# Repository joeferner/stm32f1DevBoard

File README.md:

# STM32F1xxx Dev Board

STM32F1xxx ARM Dev board with Microchip MRF24WB0MA WiFi and SD Card.

## Resources

* [Programming STM32 F2, F4 ARMs under Linux: A Tutorial from Scratch](http://www.triplespark.net/elec/pdev/arm/stm32.html)
* [stm32flash](http://code.google.com/p/stm32flash/)

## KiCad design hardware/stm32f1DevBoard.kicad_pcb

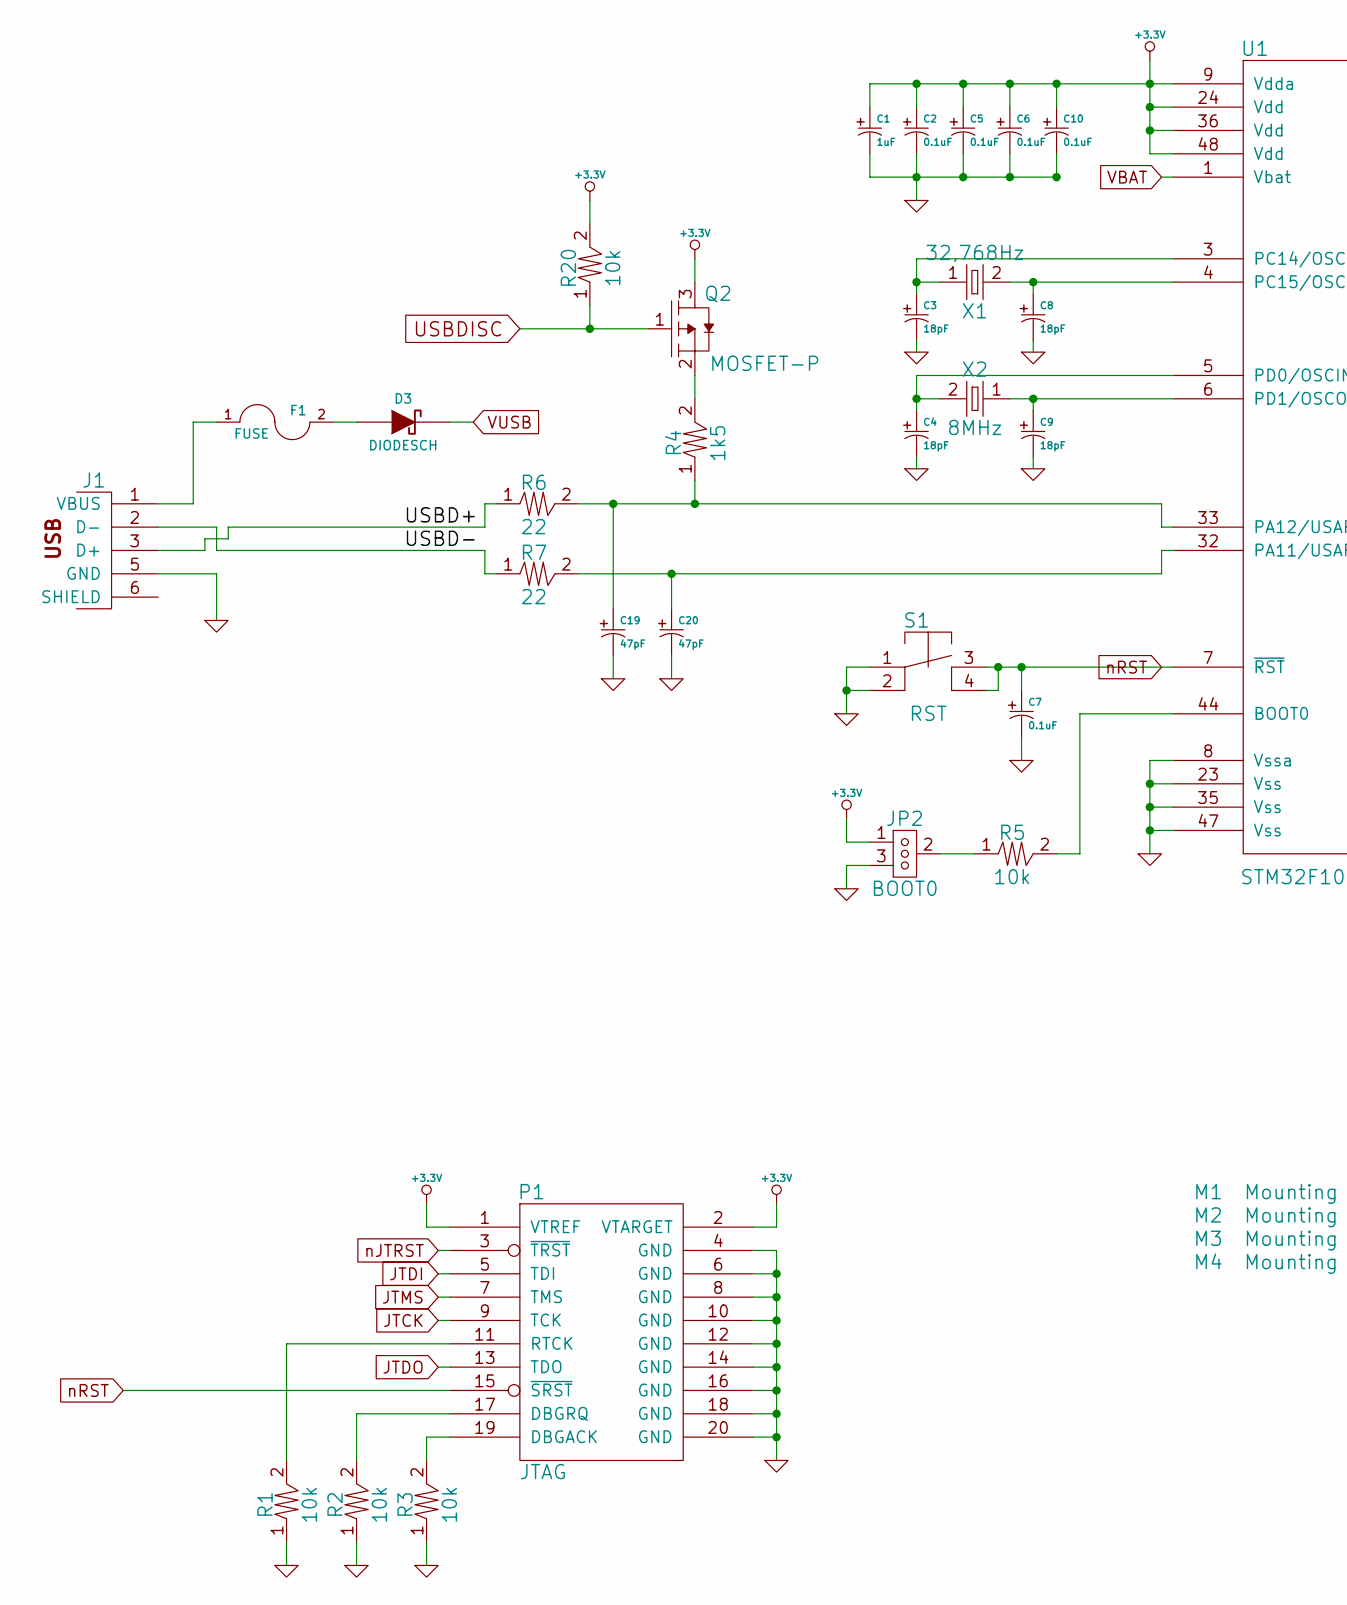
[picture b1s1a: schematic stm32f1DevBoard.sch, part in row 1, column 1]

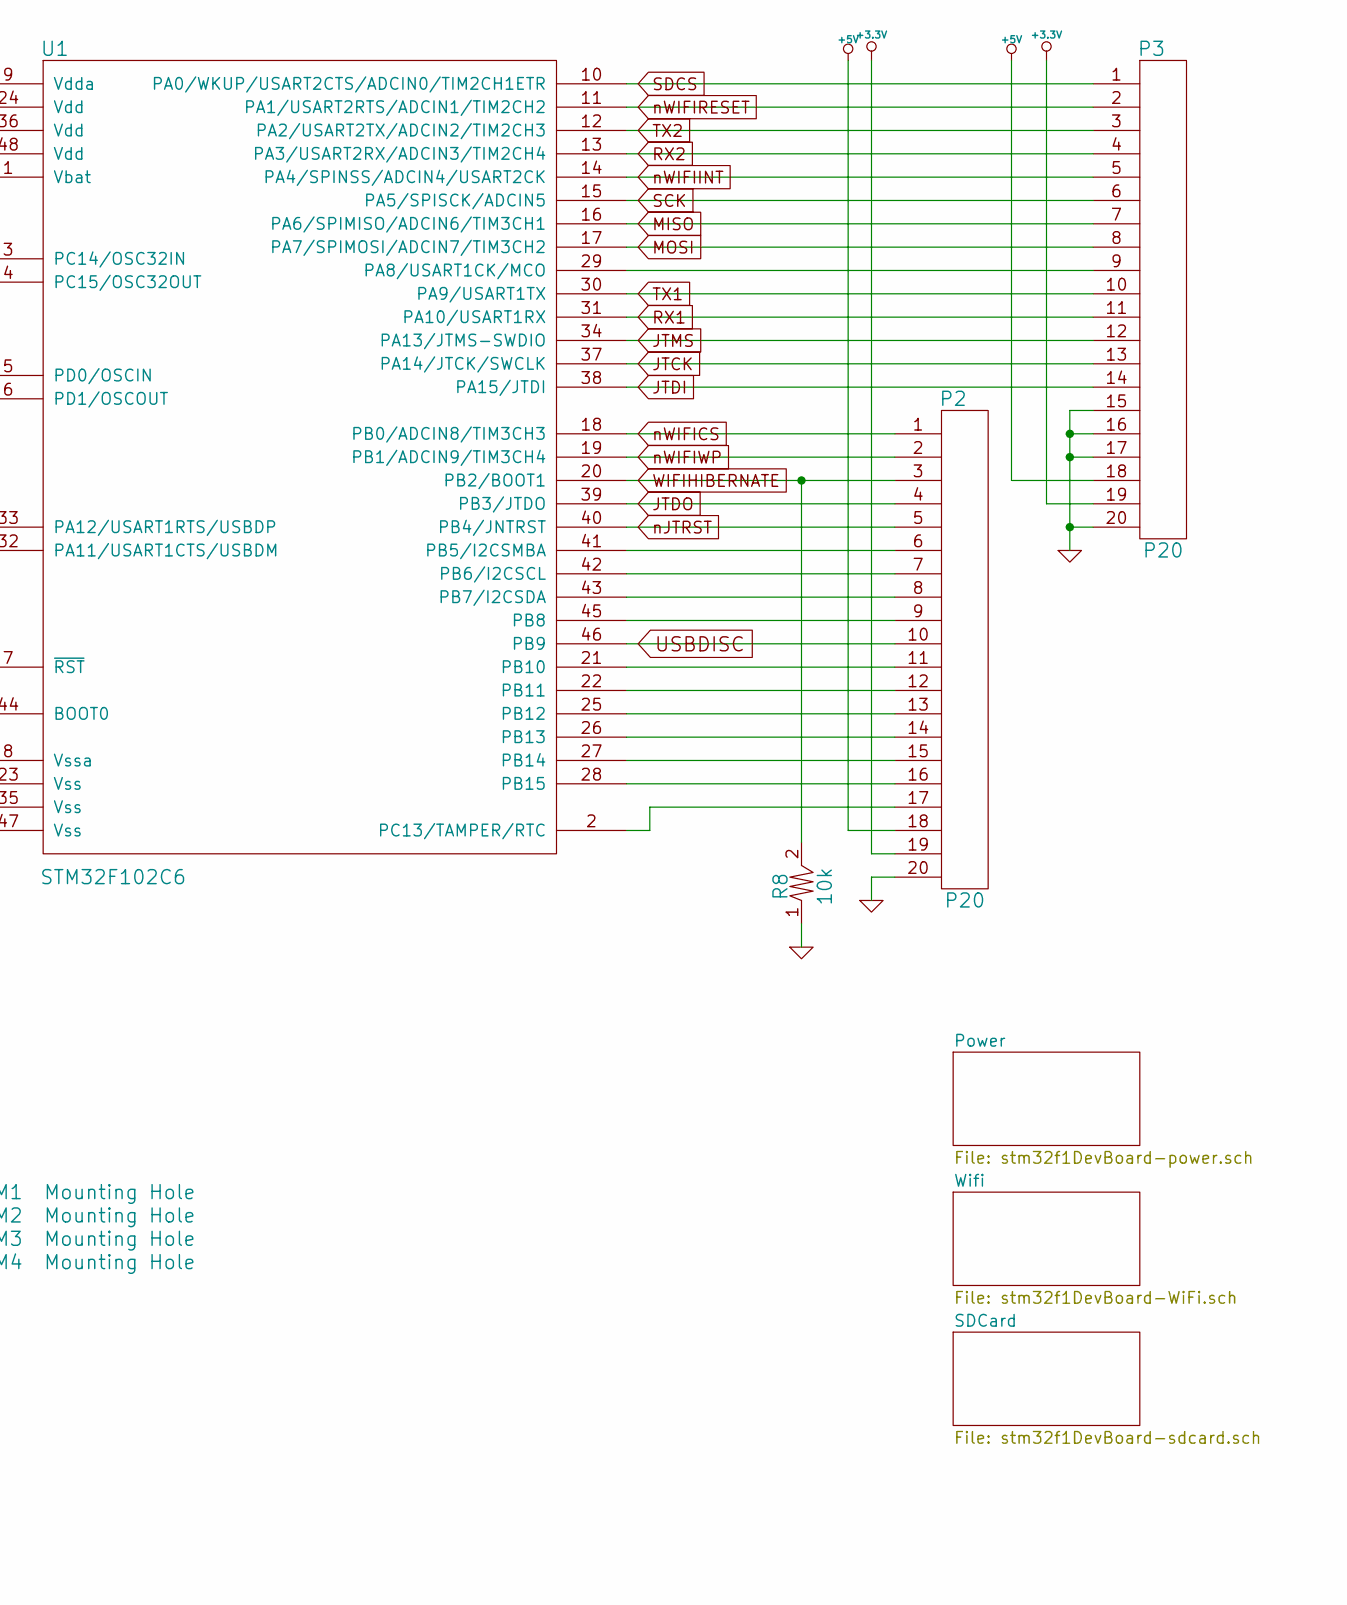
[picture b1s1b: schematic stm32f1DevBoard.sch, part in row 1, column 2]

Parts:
C1: 1uF
C2, C5, C6, C7, C10: 0.1uF
C3, C4, C8, C9: 18pF
C19, C20: 47pF
D3: DIODESCH
F1: FUSE
J1: USB_2
JP2: BOOT0
M1, M2, M3, M4: Mounting Hole
P1: JTAG
P2, P3: P20
Q2: MOSFET-P
R1, R2, R3, R5, R8, R20: 10k
R4: 1k5
R6, R7: 22
S1: RST
U1: STM32F102C6
X1: 32,768Hz
X2: 8MHz

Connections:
+3.3V: C1.1, C2.1, C5.1, C6.1, C10.1, JP2.1, P1.1 (VTREF), P1.2 (VTARGET), P2.19, P3.19, Q2.3, R20.2, U1.9 (Vdda), U1.24 (Vdd), U1.36 (Vdd), U1.48 (Vdd); also elsewhere on the board
+5V: P2.18, P3.18; also elsewhere on the board
/USBD+: J1.3 (D+), R6.1
/USBD-: J1.2 (D-), R7.1
GND: C1.2, C2.2, C3.2, C4.2, C5.2, C6.2, C7.2, C8.2, C9.2, C10.2, C19.2, C20.2, J1.5 (GND), JP2.3, P1.4 (GND), P1.6 (GND), P1.8 (GND), P1.10 (GND), P1.12 (GND), P1.14 (GND), P1.16 (GND), P1.18 (GND), P1.20 (GND), P2.20, P3.15, P3.16, P3.17, P3.20, R1.1, R2.1, R3.1, R8.1, S1.1, S1.2, U1.8 (Vssa), U1.23 (Vss), U1.35 (Vss), U1.47 (Vss); also elsewhere on the board
JTCK: P1.9 (TCK), P3.13, U1.37 (PA14/JTCK/SWCLK)
JTDI: P1.5 (TDI), P3.14, U1.38 (PA15/JTDI)
JTDO: P1.13 (TDO), P2.4, U1.39 (PB3/JTDO)
JTMS: P1.7 (TMS), P3.12, U1.34 (PA13/JTMS-SWDIO)
MISO: P3.7, U1.16 (PA6/SPIMISO/ADCIN6/TIM3CH1); also elsewhere on the board
MOSI: P3.8, U1.17 (PA7/SPIMOSI/ADCIN7/TIM3CH2); also elsewhere on the board
unnamed: P3.9, U1.29 (PA8/USART1CK/MCO)
unnamed: P2.16, U1.28 (PB15)
unnamed: P2.15, U1.27 (PB14)
unnamed: P2.14, U1.26 (PB13)
unnamed: P2.9, U1.45 (PB8)
unnamed: P2.13, U1.25 (PB12)
unnamed: P2.8, U1.43 (PB7/I2CSDA)
unnamed: P2.17, U1.2 (PC13/TAMPER/RTC)
unnamed: P2.12, U1.22 (PB11)
unnamed: P2.11, U1.21 (PB10)
unnamed: P2.7, U1.42 (PB6/I2CSCL)
unnamed: P2.6, U1.41 (PB5/I2CSMBA)
unnamed: C3.1, U1.3 (PC14/OSC32IN), X1.1
unnamed: D3.1 (A), F1.2
unnamed: F1.1, J1.1 (VBUS)
unnamed: Q2.2, R4.2
unnamed: P1.11 (RTCK), R1.2
unnamed: P1.19 (DBGACK), R3.2
unnamed: P1.17 (DBGRQ), R2.2
unnamed: C20.1, R7.2, U1.32 (PA11/USART1CTS/USBDM)
unnamed: C8.1, U1.4 (PC15/OSC32OUT), X1.2
unnamed: C4.1, U1.5 (PD0/OSCIN), X2.2
unnamed: R5.2, U1.44 (BOOT0)
unnamed: JP2.2, R5.1
unnamed: C19.1, R4.1, R6.2, U1.33 (PA12/USART1RTS/USBDP)
unnamed: C9.1, U1.6 (PD1/OSCOUT), X2.1
RX1: P3.11, U1.31 (PA10/USART1RX)
RX2: P3.4, U1.13 (PA3/USART2RX/ADCIN3/TIM2CH4)
SCK: P3.6, U1.15 (PA5/SPISCK/ADCIN5); also elsewhere on the board
SDCS: P3.1, U1.10 (PA0/WKUP/USART2CTS/ADCIN0/TIM2CH1ETR); also elsewhere on the board
TX1: P3.10, U1.30 (PA9/USART1TX)
TX2: P3.3, U1.12 (PA2/USART2TX/ADCIN2/TIM2CH3)
USBDISC: P2.10, Q2.1, R20.1, U1.46 (PB9)
VBAT: U1.1 (Vbat); also elsewhere on the board
VUSB: D3.2 (K); also elsewhere on the board
WIFIHIBERNATE: P2.3, R8.2, U1.20 (PB2/BOOT1); also elsewhere on the board
nJTRST: P1.3 (~TRST), P2.5, U1.40 (PB4/JNTRST)
nRST: C7.1, P1.15 (~SRST), S1.3, S1.4, U1.7 (~RST)
nWIFICS: P2.1, U1.18 (PB0/ADCIN8/TIM3CH3); also elsewhere on the board
nWIFIINT: P3.5, U1.14 (PA4/SPINSS/ADCIN4/USART2CK); also elsewhere on the board
nWIFIRESET: P3.2, U1.11 (PA1/USART2RTS/ADCIN1/TIM2CH2); also elsewhere on the board
nWIFIWP: P2.2, U1.19 (PB1/ADCIN9/TIM3CH4); also elsewhere on the board

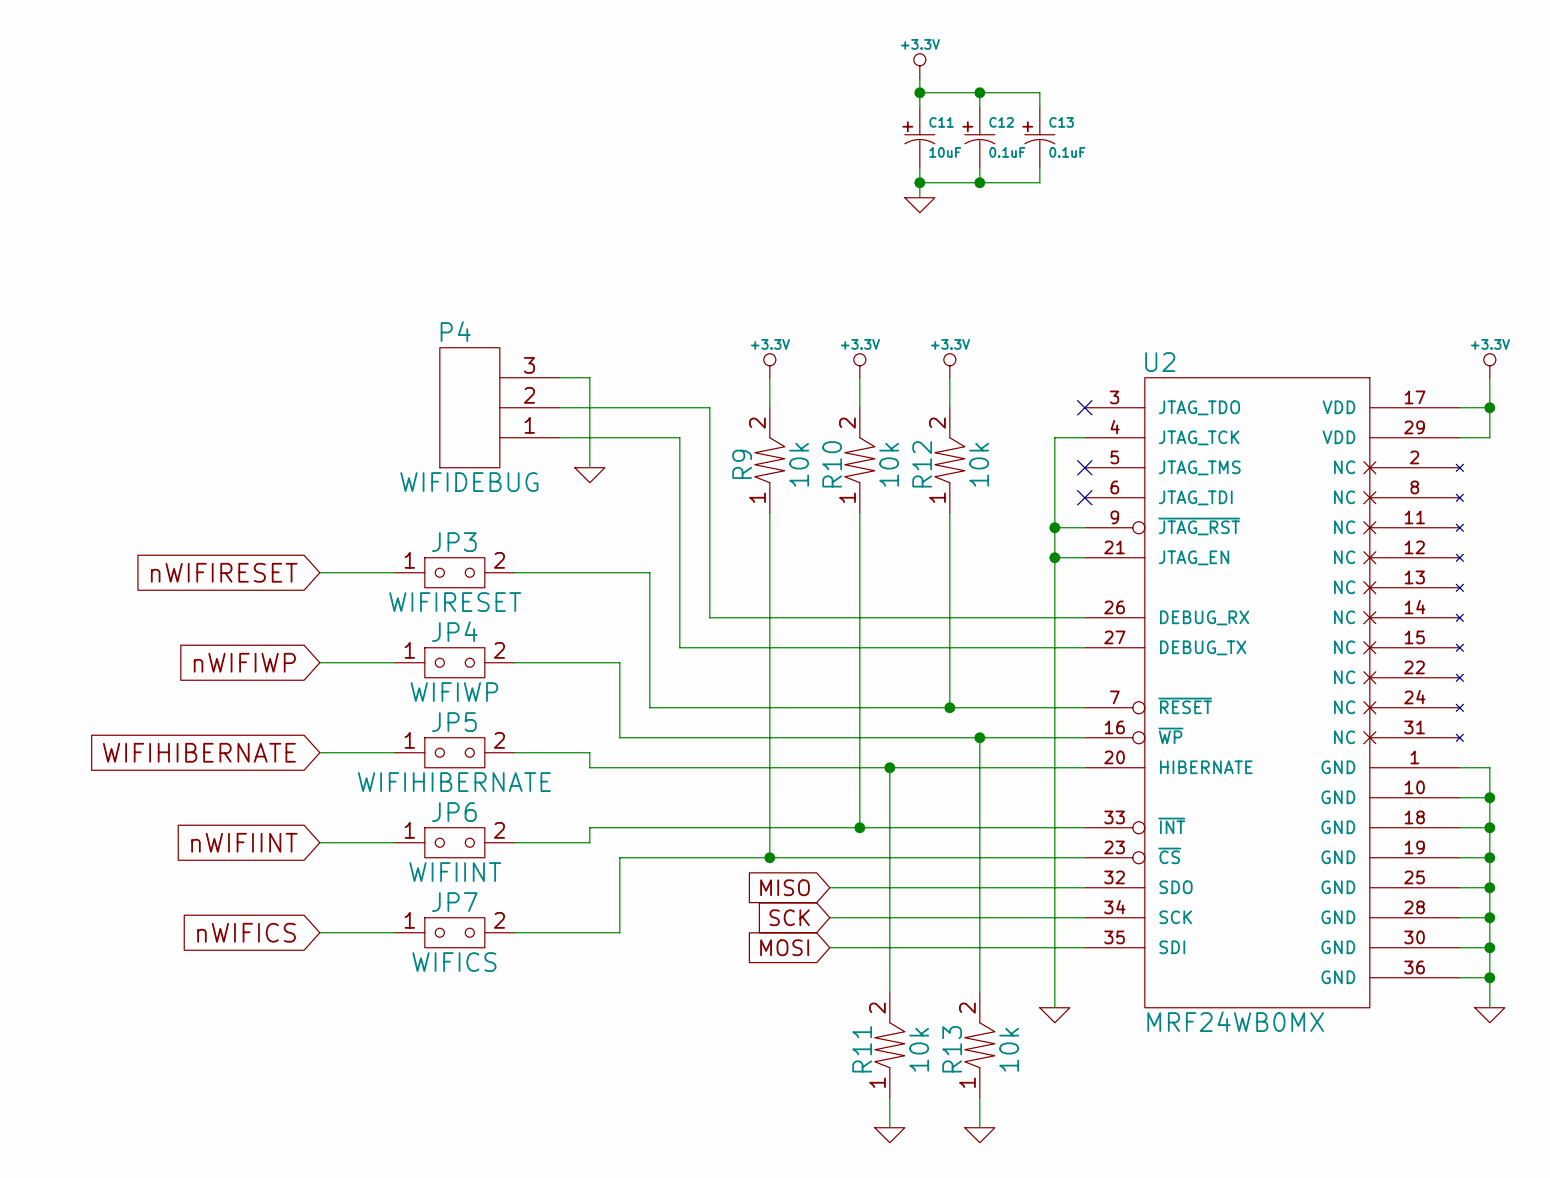
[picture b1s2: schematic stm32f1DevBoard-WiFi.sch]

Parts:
C11: 10uF
C12, C13: 0.1uF
JP3: WIFIRESET
JP4: WIFIWP
JP5: WIFIHIBERNATE
JP6: WIFIINT
JP7: WIFICS
P4: WIFIDEBUG
R9, R10, R11, R12, R13: 10k
U2: MRF24WB0MX

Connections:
+3.3V: C11.1, C12.1, C13.1, R9.2, R10.2, R12.2, U2.17 (VDD), U2.29 (VDD); also elsewhere on the board
GND: C11.2, C12.2, C13.2, P4.3, R11.1, R13.1, U2.1 (GND), U2.4 (JTAG_TCK), U2.9 (~JTAG_RST), U2.10 (GND), U2.18 (GND), U2.19 (GND), U2.21 (JTAG_EN), U2.25 (GND), U2.28 (GND), U2.30 (GND), U2.36 (GND); also elsewhere on the board
MISO: U2.32 (SDO); also elsewhere on the board
MOSI: U2.35 (SDI); also elsewhere on the board
unnamed: JP4.2, R13.2, U2.16 (~WP)
unnamed: JP5.2, R11.2, U2.20 (HIBERNATE)
unnamed: JP3.2, R12.1, U2.7 (~RESET)
unnamed: JP7.2, R9.1, U2.23 (~CS)
unnamed: JP6.2, R10.1, U2.33 (~INT)
unnamed: P4.2, U2.26 (DEBUG_RX)
unnamed: P4.1, U2.27 (DEBUG_TX)
SCK: U2.34 (SCK); also elsewhere on the board
WIFIHIBERNATE: JP5.1; also elsewhere on the board
nWIFICS: JP7.1; also elsewhere on the board
nWIFIINT: JP6.1; also elsewhere on the board
nWIFIRESET: JP3.1; also elsewhere on the board
nWIFIWP: JP4.1; also elsewhere on the board

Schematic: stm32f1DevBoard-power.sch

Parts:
BT1: BATTERY
C14, C18: 100uF
C15, C16: 10uF
D1: DIODESCH
D2: POWERLED
J2: POWER_JACK
JP8: BATTERYENABLE
Q1: MOSFET-P
R14: 68k
R15: 33k
R16, R17: 10k
R18: 100
U3: LM358
U4: VREG-X-5
U5: VREG-5-3.3

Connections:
+3.3V: C16.1, C18.1, JP8.1, R18.1, U5.2 (VO), U5.4 (TAB); also elsewhere on the board
+5V: C14.1, C15.1, Q1.2, R16.2, U3.8 (V+), U4.3 (VO), U5.3 (VI); also elsewhere on the board
GND: BT1.2 (-), C14.2, C15.2, C16.2, C18.2, D2.2 (K), J2.2, J2.3, R15.1, R17.1, U3.4 (V-), U4.2 (GND), U4.4 (TAB), U5.1 (GND); also elsewhere on the board
unnamed: D2.1 (A), R18.2
unnamed: R14.1, R15.2, U3.3 (+)
unnamed: R16.1, R17.2, U3.2 (-)
unnamed: U3.1, U3.5 (+)
unnamed: Q1.1, U3.6 (-), U3.7
unnamed: BT1.1 (+), JP8.3
unnamed: D1.1 (A), J2.1
VBAT: JP8.2; also elsewhere on the board
VIN: D1.2 (K), R14.2, U4.1 (VI)
VUSB: Q1.3; also elsewhere on the board

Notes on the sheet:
Pin2 = 2.5V Pin3 = 2.5V at 7.65V

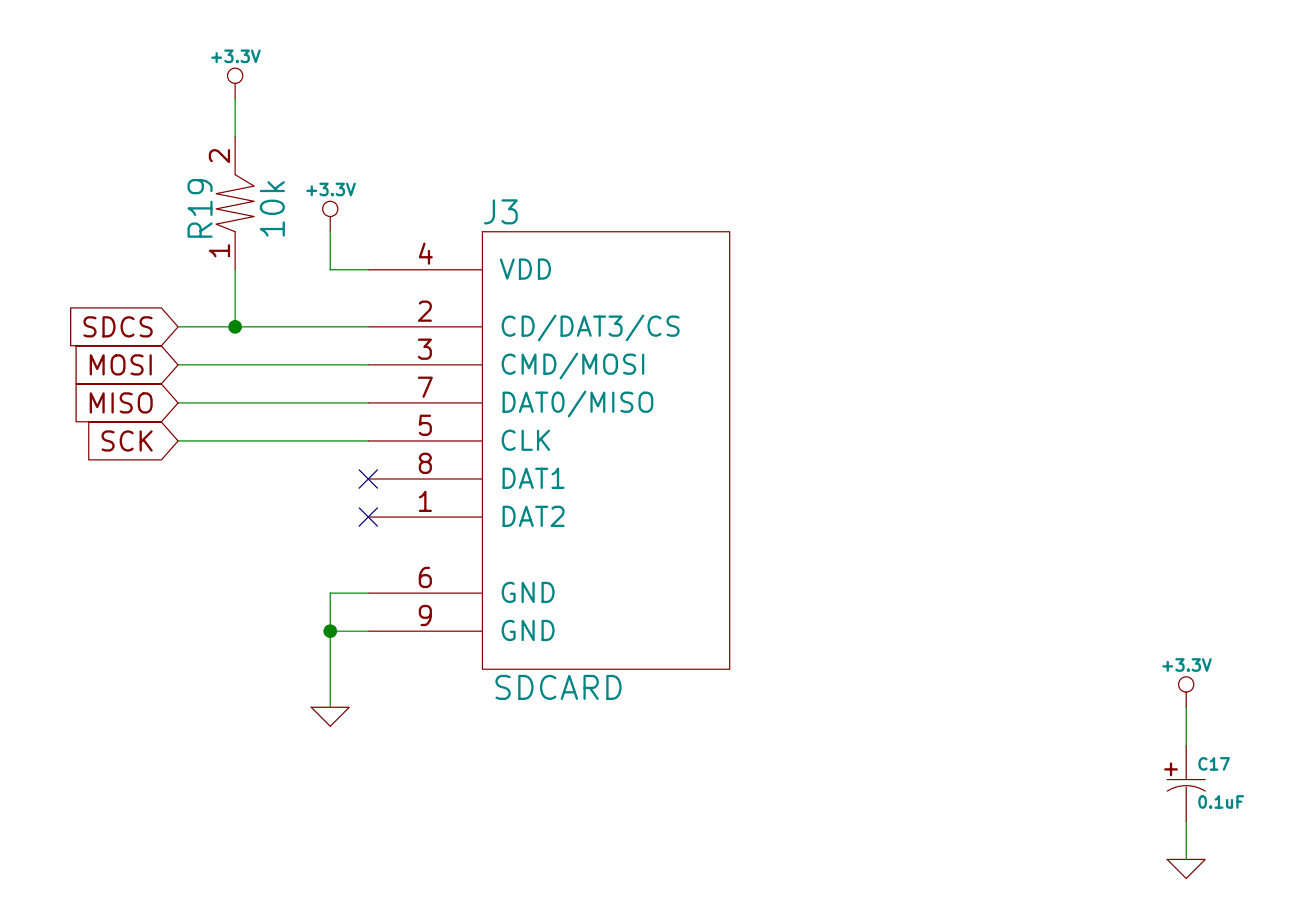
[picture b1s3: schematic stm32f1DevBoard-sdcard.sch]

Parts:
C17: 0.1uF
J3: SDCARD
R19: 10k

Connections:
+3.3V: C17.1, J3.4 (VDD), R19.2; also elsewhere on the board
GND: C17.2, J3.6 (GND), J3.9 (GND); also elsewhere on the board
MISO: J3.7 (DAT0/MISO); also elsewhere on the board
MOSI: J3.3 (CMD/MOSI); also elsewhere on the board
SCK: J3.5 (CLK); also elsewhere on the board
SDCS: J3.2 (CD/DAT3/CS), R19.1; also elsewhere on the board

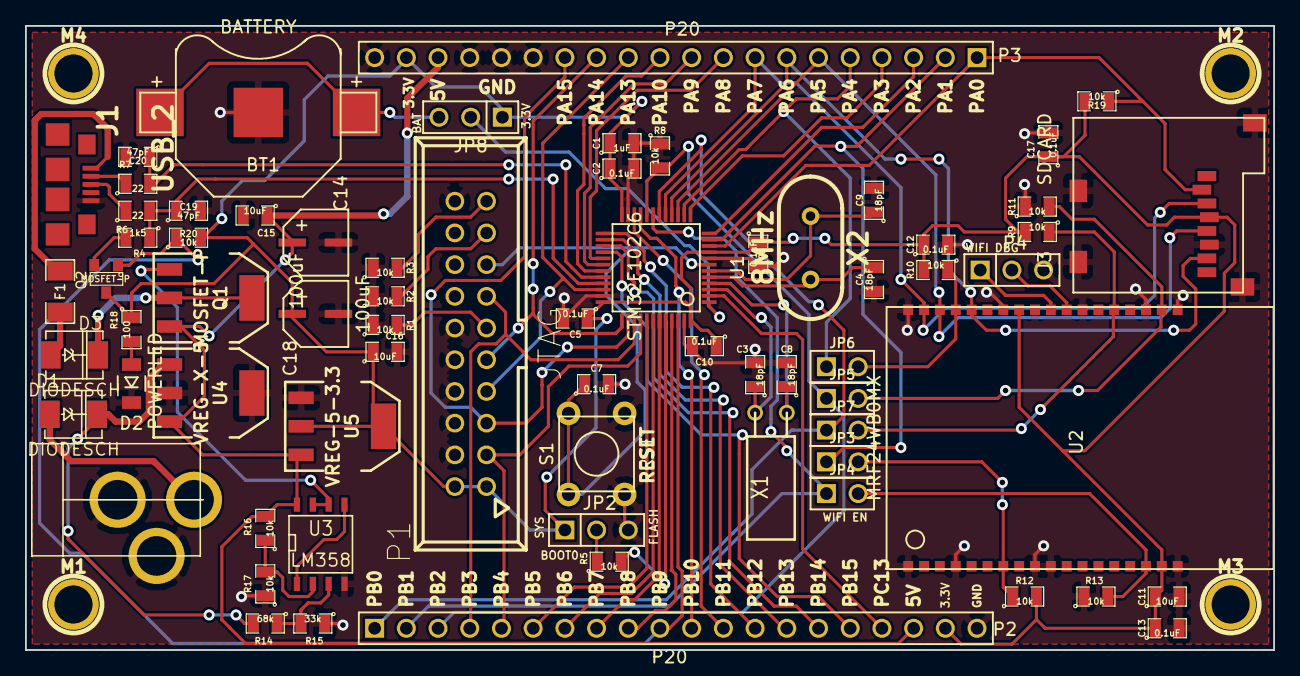
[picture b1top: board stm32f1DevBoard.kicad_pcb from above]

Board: 2 copper layers, 100.0 x 50.0 mm, 73 parts (0 on the bottom side), 68 nets.

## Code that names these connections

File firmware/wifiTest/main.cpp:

#include <wirish/wirish.h>
#include <mrf24w/mrf24w.h>
#include <string.h>

#define SDCARD_CS           PA0
#define SDCARD_SPI          1

#define WIFI_CS             PB0
#define WIFI_INT            PA4
#define WIFI_CONNECTION_LED PB5
#define WIFI_RESET          PA1
#define WIFI_WP             PB1
#define WIFI_HIBERNATE      PB2
#define WIFI_SPI            SDCARD_SPI

#define ECHO_PORT 8000

uint8_t wifiLocalIp[] = {192, 168, 1, 99};
uint8_t wifiGatewayIp[] = {192, 168, 1, 1};
uint8_t wifiSubnetMask[] = {255, 255, 255, 0};
const char* wifiSSID = "STMWIFI"; //"STMTEST";
const char* wifiSecurityPassphrase = "";
uint8_t wifiSecurityType = WF_SECURITY_OPEN;
uint8_t wifiWirelessMode = WF_INFRASTRUCTURE; //WF_ADHOC;

HardwareSPI spi1(WIFI_SPI);
Mrf24w wifi(spi1, WIFI_CS, WIFI_INT);

void wifiProcessEvent(uint8_t event, uint16_t eventInfo, uint8_t* extraInfo);

void setup() {
  Serial1.begin(19200);
  Serial1.println("begin");

  enableDebugPorts();
  //delay(5000);
  //disableDebugPorts();

  pinMode(SDCARD_CS, OUTPUT);
  digitalWrite(SDCARD_CS, HIGH);
  pinMode(WIFI_CS, OUTPUT);
  digitalWrite(WIFI_CS, HIGH);

  pinMode(WIFI_RESET, OUTPUT);
  pinMode(WIFI_HIBERNATE, OUTPUT);
  digitalWrite(WIFI_HIBERNATE, LOW);
  pinMode(WIFI_WP, OUTPUT);
  digitalWrite(WIFI_WP, LOW);
  pinMode(WIFI_CONNECTION_LED, OUTPUT);
  digitalWrite(WIFI_CONNECTION_LED, LOW);
  spi1.begin(SPI_4_5MHZ, MSBFIRST, 0);

  Serial1.println("wifi setup");
  digitalWrite(WIFI_RESET, LOW);
  delay(100);
  digitalWrite(WIFI_RESET, HIGH);

  wifi.setProcessEventFn(wifiProcessEvent);
  Serial1.println("wifi begin");
  wifi.setLocalIp(wifiLocalIp);
  wifi.setGatewayIp(wifiGatewayIp);
  wifi.setSubnetMask(wifiSubnetMask);
  wifi.setSSID(wifiSSID);
  wifi.setSecurityPassphrase(wifiSecurityPassphrase);
  wifi.setSecurityType(wifiSecurityType);
  wifi.setWirelessMode(wifiWirelessMode);
  wifi.begin();
  Serial1.println("wifi begin complete");

  //wifi.scan(WF_SCAN_ALL);

  wifi.connect();

  //uip_listen(HTONS(ECHO_PORT));
}

int ssss = 0;
struct uip_udp_conn *c;

void loop() {
  wifi.loop();

  while (Serial1.available() > 0) {
    uint8_t b = Serial1.read();
    if (b == 'r') {
      Serial1.println("rebooting 1sec");
      delay(1000);
      nvic_sys_reset();
    }

    if (b == 'c') {
      uip_ipaddr_t addr;

      uip_ipaddr(&addr, 192, 168, 1, 100);
      c = uip_udp_new(&addr, HTONS(1234));
      ssss = 0;
      if (c != NULL) {
        uip_udp_bind(c, HTONS(1234));
        Serial1.println("udp_new");
      } else {
        Serial1.println("udp_new fail");
      }
    }
  }
}

extern "C" void echo_udp_appcall() {
  Serial1.print("echo_udp_appcall: ");
  Serial1.println(ssss);

  if (uip_newdata()) {
    Serial1.print("new data: ");
    Serial1.println(uip_datalen());
    for (int i = 0; i < uip_datalen(); i++) {
      char ch = (char)((uint8_t*)uip_appdata)[i];
      Serial1.print(ch);
    }
    Serial1.println();
  } else if (uip_poll()) {
    if ((ssss % 10) == 0) {
      uip_send("test", 4);
    }
    ssss++;
  }
}

extern "C" void echo_appcall() {
  Serial1.println("echo_appcall");

  if (uip_conn->lport == HTONS(ECHO_PORT)) {
    struct echo_state* s = uip_conn->appstate;

    if (uip_connected()) {
      s->state = ECHO_STATE_WELCOME_SENT;
      uip_send("start echo!", strlen("start echo!"));
    }

    if (uip_acked() && s->state == ECHO_STATE_WELCOME_SENT) {
      s->state = ECHO_STATE_WELCOME_ACKED;
    }

    if (uip_newdata()) {
      uip_send(uip_appdata, uip_datalen());
    }

    if (uip_rexmit()) {
      switch (s->state) {
        case ECHO_STATE_WELCOME_SENT:
          uip_send("start echo!", strlen("start echo!"));
          break;
        case ECHO_STATE_WELCOME_ACKED:
          // don't have the data anymore
          break;
      }
    }
  }
}

extern "C" void uip_log(char *msg) {
  Serial1.println(msg);
}

void wifiProcessEvent(uint8_t event, uint16_t eventInfo, uint8_t* extraInfo) {
  switch (event) {
    case WF_EVENT_CONNECTION_SUCCESSFUL:
    case WF_EVENT_CONNECTION_REESTABLISHED:
      digitalWrite(WIFI_CONNECTION_LED, HIGH);
      break;

    case WF_EVENT_CONNECTION_PERMANENTLY_LOST:
    case WF_EVENT_CONNECTION_TEMPORARILY_LOST:
    case WF_EVENT_CONNECTION_FAILED:
      digitalWrite(WIFI_CONNECTION_LED, LOW);
      break;
  }
}

// Force init to be called *first*, i.e. before static object allocation.
// Otherwise, statically allocated objects that need libmaple may fail.

__attribute__((constructor)) void premain() {
  init();
}

int main(void) {
  setup();

  while (true) {
    loop();
  }

  return 0;
}

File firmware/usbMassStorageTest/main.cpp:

#include <wirish/wirish.h>
#include <usbMassStorage/usbMassStorage.h>
#include <sdfat/Sd2Card.h>
#include <sdfat/SdFat.h>

/**
 * This example requires the maple-sdfat library (http://code.google.com/p/maple-sdfat/).
 * 
 * When the example starts it creates two files /PROC/REBOOT and /PROC/BOOTLOAD
 * If you write anything to these files from the host computer it will reboot or
 * enter the bootloader respectively.
 * 
 *   Connections:
 *      PA0             -> SDCard.CS
 *      PA7 (SPI1 MOSI) -> SDCard.DI
 *      PA6 (SPI1 MISO) -> SDCard.DO
 *      PA5 (SPI1 SCK)  -> SDCard.CLK
 */
#define SDCARD_CS  PA0
#define SDCARD_SPI 1

uint32_t MAL_massBlockCount[2];
uint32_t MAL_massBlockSize[2];
uint32_t rebootFileBlock;
uint32_t bootLoadFileBlock;

HardwareSPI spi1(SDCARD_SPI);
Sd2Card sdcard(spi1);
SdVolume sdVolume;

uint8_t initSdCardSize();
uint8_t initCard();
void reboot();
void enterBootloader();

void setup() {
  Serial1.begin(9600);
  Serial1.println("begin");

  enableDebugPorts();
  //delay(5000);
  //disableDebugPorts();
  
  Serial1.println("spi begin");
  spi1.begin(SPI_QUARTER_SPEED, MSBFIRST, 0);
  Serial1.println("sdcard begin");
  sdcard.init(SPI_QUARTER_SPEED, SDCARD_CS);
  sdVolume.init(&sdcard, 0);

  initSdCardSize();
  initCard();

  Serial1.println("USBMassStorage.begin");
  USBMassStorage.begin();

  Serial1.println("setup complete");
}

void loop() {
  USBMassStorage.loop();
}

// Force init to be called *first*, i.e. before static object allocation.
// Otherwise, statically allocated objects that need libmaple may fail.

__attribute__((constructor)) void premain() {
  init();
}

int main(void) {
  setup();

  while (true) {
    loop();
  }

  return 0;
}

/**
 * Initializes the USBMassStorage driver with the size of the SDCard. 
 */
uint8_t initSdCardSize() {
  Serial1.println("initSdCardSize");
  uint32_t numberOfBlocks = sdcard.cardSize();
  if (numberOfBlocks == 0) {
    Serial1.println("could not get card size");
    return false;
  }
  MAL_massBlockCount[0] = numberOfBlocks;
  MAL_massBlockCount[1] = 0;
  MAL_massBlockSize[0] = 512;
  MAL_massBlockSize[1] = 0;
  Serial1.print("cardSize = ");
  Serial1.println(numberOfBlocks * 512);
  return true;
}

/**
 * Creates the /PROC/REBOOT and /PROC/BOOTLOAD files to allow
 * remote reboot and bootloader respectively.
 */
uint8_t initCard() {
  Serial1.println("initCard");
  SdFile root, procDir, rebootFile, bootLoadFile;

  // open the root directory
  if (!root.openRoot(&sdVolume)) {
    Serial1.println("failed to openRoot");
    return false;
  }

  // open the /PROC directory
  if (!procDir.open(root, "PROC", O_READ)) {
    if (!procDir.makeDir(root, "PROC")) {
      Serial1.println("failed to create proc");
      return false;
    }
  }

  // create /PROC/REBOOT file and write a '0' to it.
  if (!rebootFile.open(procDir, "REBOOT", O_WRITE | O_CREAT | O_TRUNC)) {
    Serial1.println("Could not create /PROC/REBOOT");
    return false;
  }
  rebootFile.write('0');
  rebootFile.close();
  rebootFileBlock = rebootFile.firstCluster() * sdVolume.blocksPerCluster();
  Serial1.print("/PROC/REBOOT: ");
  Serial1.println(rebootFileBlock);

  // create /PROC/BOOTLOAD file and write a '0' to it.
  if (!bootLoadFile.open(procDir, "BOOTLOAD", O_WRITE | O_CREAT | O_TRUNC)) {
    Serial1.println("Could not create /PROC/BOOTLOAD");
    return false;
  }
  bootLoadFile.write('0');
  bootLoadFile.close();
  bootLoadFileBlock = bootLoadFile.firstCluster() * sdVolume.blocksPerCluster();
  Serial1.print("/PROC/BOOTLOAD: ");
  Serial1.println(bootLoadFileBlock);

  procDir.close();
  root.close();
  return true;
}

/*
 * The following methods are used by the USBMassStorage driver to read and write to the SDCard.  
 */

extern "C" uint16_t usb_mass_mal_init(uint8_t lun) {
  //Serial1.println("usb_mass_mal_init");
  return 0;
}

extern "C" uint16_t usb_mass_mal_get_status(uint8_t lun) {
  //Serial1.print("usb_mass_mal_get_status: ");
  //Serial1.println(sdcard.errorCode());
  return sdcard.errorCode();
}

extern "C" uint16_t usb_mass_mal_write_memory(uint8_t lun, uint32_t memoryOffset, uint8_t *writebuff, uint16_t transferLength) {
  //Serial1.println("usb_mass_mal_write_memory");
  uint32_t block = memoryOffset / 512;
  if (block == rebootFileBlock) {
    reboot();
    return USB_MASS_MAL_SUCCESS;
  }
  if (block == bootLoadFileBlock) {
    enterBootloader();
    return USB_MASS_MAL_SUCCESS;
  }

  if (lun != 0) {
    return USB_MASS_MAL_FAIL;
  }
  if (sdcard.writeBlock(block, writebuff)) {
    return USB_MASS_MAL_SUCCESS;
  }
  return USB_MASS_MAL_FAIL;
}

extern "C" uint16_t usb_mass_mal_read_memory(uint8_t lun, uint32_t memoryOffset, uint8_t *readbuff, uint16_t transferLength) {
  //Serial1.println("usb_mass_mal_read_memory");
  if (lun != 0) {
    return USB_MASS_MAL_FAIL;
  }
  if (sdcard.readBlock(memoryOffset / 512, readbuff)) {
    return USB_MASS_MAL_SUCCESS;
  }
  return USB_MASS_MAL_FAIL;
}

extern "C" void usb_mass_mal_format() {
}

/*
 * Helper methods to reboot and enter the bootloader 
 */

void reboot() {
  Serial1.println("reset");
  nvic_sys_reset();
  while (1);
}

#define RESET_DELAY 100000

static void wait_reset(void) {
  delay_us(RESET_DELAY);
  nvic_sys_reset();
}

#define STACK_TOP 0x20000800
#define EXC_RETURN 0xFFFFFFF9
#define DEFAULT_CPSR 0x61000000

void enterBootloader() {
  Serial1.println("bootloader");

  // Got the magic sequence -> reset, presumably into the bootloader.
  // Return address is wait_reset, but we must set the thumb bit.
  uintptr_t target = (uintptr_t) wait_reset | 0x1;
  asm volatile("mov r0, %[stack_top]      \n\t" // Reset stack
            "mov sp, r0                \n\t"
            "mov r0, #1                \n\t"
            "mov r1, %[target_addr]    \n\t"
            "mov r2, %[cpsr]           \n\t"
            "push {r2}                 \n\t" // Fake xPSR
            "push {r1}                 \n\t" // PC target addr
            "push {r0}                 \n\t" // Fake LR
            "push {r0}                 \n\t" // Fake R12
            "push {r0}                 \n\t" // Fake R3
            "push {r0}                 \n\t" // Fake R2
            "push {r0}                 \n\t" // Fake R1
            "push {r0}                 \n\t" // Fake R0
            "mov lr, %[exc_return]     \n\t"
            "bx lr"
            :
            : [stack_top] "r" (STACK_TOP),
            [target_addr] "r" (target),
            [exc_return] "r" (EXC_RETURN),
            [cpsr] "r" (DEFAULT_CPSR)
            : "r0", "r1", "r2");
}

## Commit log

2012-12-13 initial
2012-12-13 more schematic
2012-12-13 makefile
2012-12-13 readme
2012-12-15 power
2012-12-16 wifi and sdcard
2012-12-16 seperate into sheets
2012-12-19 more mods
2012-12-19 pcb initial layout
2012-12-20 switched transistor
2012-12-20 changed to p-ch mosfet
2012-12-28 layout complete
2012-12-28 labels
2013-01-02 more board work
2013-01-02 using kicadcloud files
2013-01-10 new v1 - with soldermask
2013-01-11 sdcardTest initial
2013-01-11 working
2013-01-11 ignore build dir
2013-01-11 getting sdcard working
2013-01-12 working sdcard size
2013-01-14 remove link to sdcard
2013-01-14 added sdcard as submodule
2013-01-14 starting usb mass storage work
2013-01-14 working on mass
2013-01-14 remove sdcard
2013-01-14 fix sdcard
2013-01-15 removed sdcard submodule
2013-01-15 usb test compile
2013-01-16 patch
2013-01-16 removed libmaple
2013-01-16 almos
2013-01-16 print block0
2013-01-16 read first block
2013-01-17 changed Sd2Card to SdCard
2013-01-17 switched to sdfat library
2013-01-17 remove links
2013-01-17 added submodules
2013-01-17 change make
2013-01-17 need to do it as file instead of submodule
2013-01-17 new version
2013-01-17 changed libmaple to submodule
2013-01-19 added pull resistor on sdcard cs
2013-01-19 using new libmaple which allows overriding USB
2013-01-22 reboot and bootloader
2013-01-22 updates to schematic
2013-01-22 wifi test
2013-01-22 update test
2013-01-28 simple test working on board
2013-01-28 added serial out
2013-01-29 fixed sdcard
2013-02-01 libmaple update
2013-02-01 usb renumber
2013-02-01 update to use jtag
2013-02-01 pin remap
2013-02-13 update hardware
2013-02-13 update make files
2013-02-16 connection successful
2013-02-21 working send/recv with errors
2013-04-05 new hardware
